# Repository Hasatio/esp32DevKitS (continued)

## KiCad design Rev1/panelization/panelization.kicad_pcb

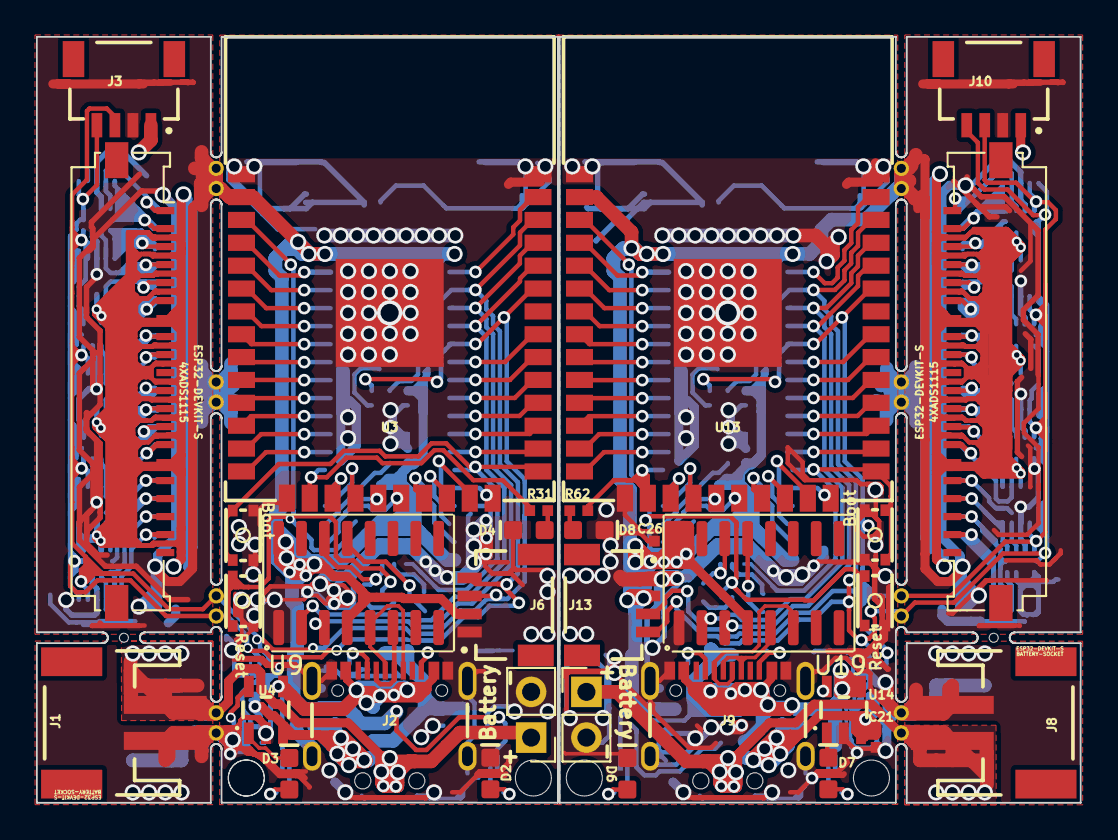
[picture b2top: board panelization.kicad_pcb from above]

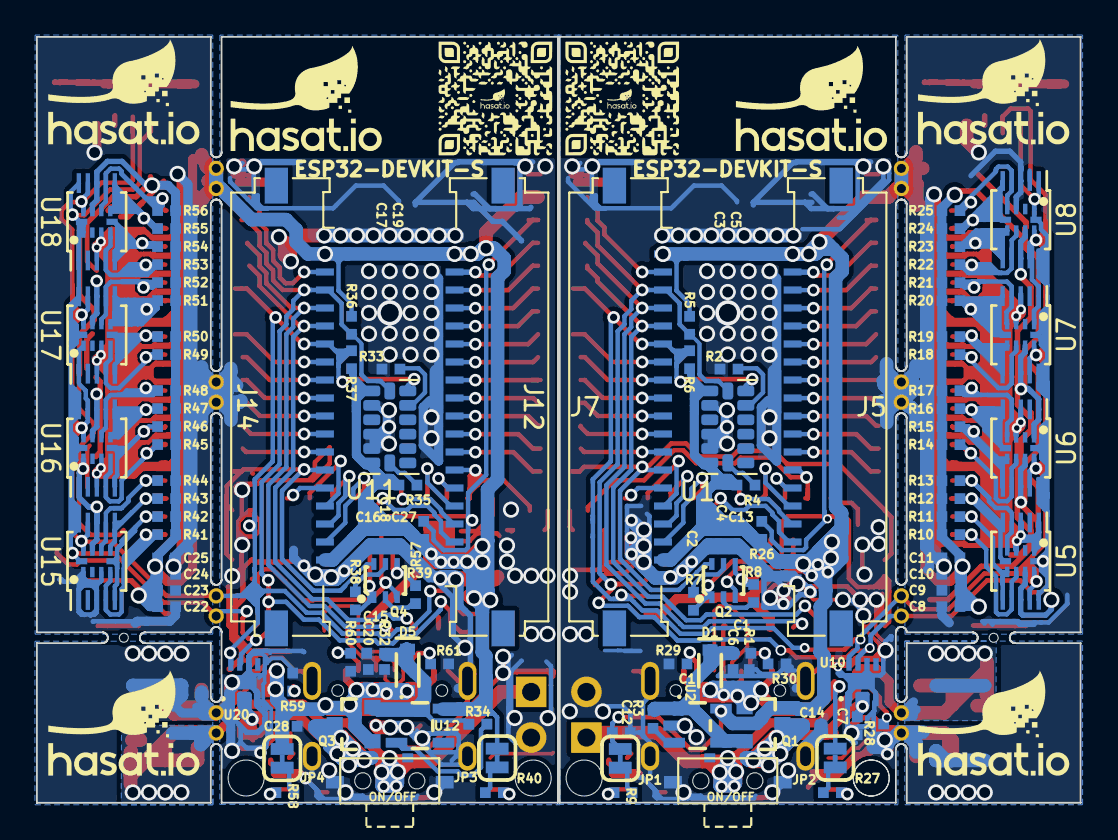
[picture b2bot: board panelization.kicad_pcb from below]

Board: 2 copper layers, 58.0 x 42.5 mm, 164 parts (124 on the bottom side), 146 nets.

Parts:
>NAME: >VALUE; QFN-10-RSE
>NAME#2, >NAME#3, >NAME#4, >NAME#5, >NAME#6, >NAME#7, >NAME#8: >VALUE; QFN-10-RSE
C1, C2, C3, C8, C9, C10, C11, C13, C15, C16, C17, C22, C23, C24, C25, C27: 1.0uF; 0402-TIGHT
C4, C5, C18, C19: 10uF; 0402-TIGHT
C6, C7, C20, C21: 4.7uF; 0402-TIGHT
C12, C14, C26, C28: 0.1uF; 0402-TIGHT
D1, D5: S4 3A/10V/280mV; SOD-323
D2, D6: RED; LED-0603
D3, D7: Yellow; LED-0603
D4, D8: BLUE; LED-0603
J1, J8: JST_2MM_MALE; JST-2-SMD
J2, J9: USB_C_2-LAYER_PADS; USB-C-16P-2LAYER-PADS
J3, J6, J10, J13: QWIIC_RIGHT_ANGLE; JST04_1MM_RA
J4, J5, J7, J11, J12, J14: Conn_01x20; Molex_200528-0200_1x20-1MP_P1.00mm_Horizontal
JP1, JP2, JP3, JP4: JUMPER-SMT_2_NC_TRACE_SILK; SMT-JUMPER_2_NC_TRACE_SILK
Q1, Q3: DMG2305UX 20V/4.2A/52mΩ/1.4W; SOT23-3
Q2, Q4: MBT3904DW1T1; SC70-6
R1, R3, R4, R7, R8, R26, R32, R34, R35, R38, R39, R57: 10k; 0402-TIGHT
R2, R5, R6, R33, R36, R37: 4k7; 0402-TIGHT
R9, R27, R31, R40, R58, R62: 1k; 0402-TIGHT
R10, R11, R12, R13, R14, R15, R16, R17, R18, R19, R20, R21, R22, R23, R24, R25, R41, R42, R43, R44, R45, R46, R47, R48, R49, R50, R51, R52, R53, R54, R55, R56: 150k; 0402-TIGHT
R28, R59: 2.0k; 0402-TIGHT
R29, R30, R60, R61: 5.1k; 0402-TIGHT
S1, S3: Boot; TACTILE_SWITCH_SMD_2.8X1.9MM
S2, S4: Reset; TACTILE_SWITCH_SMD_2.8X1.9MM
SW1, SW2: ON/OFF; SW_SPDT_k3-1295
U1, U11: ADXL345; LGA-14_3x5mm_P0.8mm_LayoutBorder1x6y
U2, U12: SOT23-5
U3, U13: >VALUE; ESP-WROOM-32-NARROW
U4, U14: MCP73831; SOT23-5
U5, U6, U7, U8, U15, U16, U17, U18: ADS1115IDGS; TSSOP-10_3x3mm_P0.5mm
U9, U19: CH340C; SOIC-16_3.9x9.9mm_P1.27mm
U10, U20: MAX17048; DFN-8
mouse-bite-1mm-slot, mouse-bite-1mm-slot#2: VAL**; mouse-bite-1mm x2
mouse-bite-emm-slot: VAL**; mouse-bite-1mm 2
mouse-bite-emm-slot#2, mouse-bite-emm-slot#3, mouse-bite-emm-slot#4, mouse-bite-emm-slot#5, mouse-bite-emm-slot#6, mouse-bite-emm-slot#7, mouse-bite-emm-slot#8: VAL**; mouse-bite-1mm 2

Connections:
Board_0-3.3V: >NAME.8, >NAME#3.8, >NAME#7.1, >NAME#7.8, >NAME#8.8, C2.1, C3.1, C4.1, C5.1, C8.1, C9.1, C10.1, C11.1, C12.1, C13.1, J3.2, J5.2, J5.19, J6.2, J7.2, J7.19, JP1.2, R4.1, R5.1, R6.1, R10.2, R11.2, R12.2, R13.2, R14.2, R15.2, R16.2, R17.2, R18.1, R19.1, R20.1, R21.1, R22.1, R23.1, R24.1, R25.1, R26.1, U1.1 (Vdd_I/O), U1.6 (Vs), U2.5 (OUT), U3.2 (VDD), U5.8 (VDD), U6.1 (ADDR), U6.8 (VDD), U7.8 (VDD), U8.8 (VDD), U9.4 (V3), U9.16 (VCC)
Board_0-/A1: >NAME#8.7, J4.19, R10.1, U5.7 (AIN3)
Board_0-/A2: >NAME#8.6, J4.18, R11.1, U5.6 (AIN2)
Board_0-/A3: >NAME#8.5, J4.17, R12.1, U5.5 (AIN1)
Board_0-/A4: >NAME#8.4, J4.16, R13.1, U5.4 (AIN0)
Board_0-/A5: >NAME#7.7, J4.14, R14.1, U6.7 (AIN3)
Board_0-/A6: >NAME#7.6, J4.13, R15.1, U6.6 (AIN2)
Board_0-/A7: >NAME#7.5, J4.12, R16.1, U6.5 (AIN1)
Board_0-/A8: >NAME#7.4, J4.11, R17.1, U6.4 (AIN0)
Board_0-/A9: >NAME.7, J4.9, R18.2, U7.7 (AIN3)
Board_0-/A10: >NAME.6, J4.8, R19.2, U7.6 (AIN2)
Board_0-/A11: >NAME.5, J4.6, R20.2, U7.5 (AIN1)
Board_0-/A12: >NAME.4, J4.5, R21.2, U7.4 (AIN0)
Board_0-/A13: >NAME#3.7, J4.4, R22.2, U8.7 (AIN3)
Board_0-/A14: >NAME#3.6, J4.3, R23.2, U8.6 (AIN2)
Board_0-/A15: >NAME#3.5, J4.2, R24.2, U8.5 (AIN1)
Board_0-/A16: >NAME#3.4, J4.1, R25.2, U8.4 (AIN0)
Board_0-/CH340-DTR: Q2.1 (E), R7.1, U9.13 (~DTR)
Board_0-/CH340-RTS: Q2.4 (E), R8.1, U9.14 (~RTS)
Board_0-/D+: J2.A6 (D+), J2.B6 (D+), U9.5 (UD+)
Board_0-/D-: J2.A7 (D-), J2.B7 (D-), U9.6 (UD-)
Board_0-/EN: R3.2, U2.3 (EN)
Board_0-/GPIO_0/ADC2_1/QPWR: J7.14, Q2.6 (C), S1.1, S1.3, U3.25 (IO0)
Board_0-/GPIO_1/TX: J7.5, U3.35 (TXD0/IO1), U9.3 (RXD)
Board_0-/GPIO_2/ADC2_2: J7.15, U3.24 (IO2)
Board_0-/GPIO_3/RX: J7.6, U3.34 (RXD0/IO3), U9.2 (TXD)
Board_0-/GPIO_4/ADC2_0: J7.13, U3.26 (IO4)
Board_0-/GPIO_5/SD_CS: J7.10, U3.29 (IO5)
Board_0-/GPIO_6/SCK: J5.3, U3.20 (SCK/CLK)
Board_0-/GPIO_7/SDO: J7.18, U3.21 (SDO/SD0)
Board_0-/GPIO_8/SDI: J7.17, U3.22 (SDI/SD1)
Board_0-/GPIO_9/SHD: J5.6, U3.17 (SHD/SD2)
Board_0-/GPIO_10/SWP: J5.5, U3.18 (SWP/SD3)
Board_0-/GPIO_11/SCS: J5.4, U3.19 (SCS/CMD)
Board_0-/GPIO_12/ADC2_5: J5.8, U3.14 (IO12)
Board_0-/GPIO_13/ADC2_4/LED: J5.7, R31.1, U3.16 (IO13)
Board_0-/GPIO_14/ADC2_6: J5.9, U3.13 (IO14)
Board_0-/GPIO_15/ADC2_3: J7.16, U3.23 (IO15)
Board_0-/GPIO_16/RX: J7.12, U3.27 (IO16)
Board_0-/GPIO_17/TX: J7.11, U3.28 (IO17)
Board_0-/GPIO_18/SCK: J7.9, U3.30 (IO18)
Board_0-/GPIO_19/CIPO: J7.8, U3.31 (IO19)
Board_0-/GPIO_21/SDA: >NAME.1, >NAME.9, >NAME#3.9, >NAME#7.9, >NAME#8.9, J3.3, J6.3, J7.7, R6.2, U1.13 (SDA/SDI/SDIO), U3.33 (IO21), U5.9 (SDA), U6.9 (SDA), U7.1 (ADDR), U7.9 (SDA), U8.9 (SDA), U10.8 (SDA)
Board_0-/GPIO_22/SCL: >NAME.10, >NAME#3.1, >NAME#3.10, >NAME#7.10, >NAME#8.10, J3.4, J6.4, J7.4, R5.2, U1.14 (SCL/SCLK), U3.36 (IO22), U5.10 (SCL), U6.10 (SCL), U7.10 (SCL), U8.1 (ADDR), U8.10 (SCL), U10.7 (SCL)
Board_0-/GPIO_23/COPI: J7.3, U3.37 (IO23)
Board_0-/GPIO_25/ADC2_8: J5.12, U3.10 (IO25)
Board_0-/GPIO_26/ADC2_9: J5.11, U3.11 (IO26)
Board_0-/GPIO_27/ADC2_7: J5.10, U3.12 (IO27)
Board_0-/GPIO_32/ADC1_4: J5.14, U3.8 (IO32)
Board_0-/GPIO_33/ADC1_5: J5.13, U3.9 (IO33)
Board_0-/GPIO_34/ADC1_6: J5.16, U3.6 (IO34)
Board_0-/GPIO_35/ADC1_7: J5.15, U3.7 (IO35)
Board_0-/GPIO_36/ADC1_0: J5.18, U3.4 (SENSOR_VP)
Board_0-/GPIO_39/ADC1_3: J5.17, U3.5 (SENSOR_VN)
Board_0-/V: J1.2 (+), SW1.2 (B)
Board_0-/~RESET: Q2.3 (C), R26.2, S2.1, S2.3, U3.3 (EN)
Board_0-GND: >NAME.3, >NAME#3.3, >NAME#7.3, >NAME#8.1, >NAME#8.3, C1.2, C2.2, C3.2, C4.2, C5.2, C6.2, C7.2, C8.2, C9.2, C10.2, C11.2, C12.2, C13.2, C14.2, D2.C, D4.C, J1.1 (-), J2.GND, J2.GND2 (GND), J2.SHLD1 (SHLD), J2.SHLD2 (SHLD), J2.SHLD3 (SHLD), J2.SHLD4 (SHLD), J3.1, J4.7, J4.15, J5.1, J5.20, J6.1, J7.1, J7.20, R1.1, R2.2, R28.1, R29.1, R30.1, S1.2, S1.4, S2.2, S2.4, SW1.GND, U1.2 (GND), U1.4 (GND), U1.5 (GND), U2.2 (GND), U3.1 (GND), U3.15 (GND), U3.38 (GND), U3.39 (GND), U4.2 (VSS), U5.1 (ADDR), U5.3 (GND), U6.3 (GND), U7.3 (GND), U8.3 (GND), U9.1 (GND), U10.1 (CTG), U10.4 (GND), U10.6 (QSTRT), U10.9 (GND)
Board_0-Net-(D2-PadA): D2.A, R9.2
Board_0-Net-(D3-PadA): D3.A, R27.2
Board_0-Net-(D4-PadA): D4.A, R31.2
Board_0-Net-(J2-CC1): J2.A5 (CC1), R30.2
Board_0-Net-(J2-CC2): J2.B5 (CC2), R29.2
Board_0-Net-(JP1-Pad1): JP1.1, R9.1
Board_0-Net-(JP2-Pad1): JP2.1, R27.1
Board_0-Net-(Q2A-B): Q2.5 (B), R7.2
Board_0-Net-(Q2B-B): Q2.2 (B), R8.2
Board_0-Net-(U1-SDO/ADDR): R2.1, U1.12 (SDO/ADDR)
Board_0-Net-(U1-~CS): R4.2, U1.7 (~CS)
Board_0-Net-(U4-PROG): R28.2, U4.5 (PROG)
Board_0-Net-(U4-STAT): D3.C, U4.1 (STAT)
Board_0-VIN: C1.1, D1.C, Q1.2 (S), R3.1, U2.1 (IN)
Board_0-V_BATT: C7.1, C14.1, Q1.3 (D), SW1.3 (C), U4.3 (VBAT), U10.2 (CELL), U10.3 (VDD)
Board_0-V_USB: C6.1, D1.A, J2.VBUS1 (VBUS), J2.VBUS2 (VBUS), JP2.2, Q1.1 (G), R1.2, U4.4 (VIN)
Board_1-3.3V: >NAME#2.8, >NAME#4.1, >NAME#4.8, >NAME#5.8, >NAME#6.8, C16.1, C17.1, C18.1, C19.1, C22.1, C23.1, C24.1, C25.1, C26.1, C27.1, J10.2, J12.2, J12.19, J13.2, J14.2, J14.19, JP3.2, R35.1, R36.1, R37.1, R41.2, R42.2, R43.2, R44.2, R45.2, R46.2, R47.2, R48.2, R49.1, R50.1, R51.1, R52.1, R53.1, R54.1, R55.1, R56.1, R57.1, U11.1 (Vdd_I/O), U11.6 (Vs), U12.5 (OUT), U13.2 (VDD), U15.8 (VDD), U16.1 (ADDR), U16.8 (VDD), U17.8 (VDD), U18.8 (VDD), U19.4 (V3), U19.16 (VCC)
Board_1-/A1: >NAME#6.4, J11.2, R41.1, U15.4 (AIN0)
Board_1-/A2: >NAME#6.5, J11.3, R42.1, U15.5 (AIN1)
Board_1-/A3: >NAME#6.6, J11.4, R43.1, U15.6 (AIN2)
Board_1-/A4: >NAME#6.7, J11.5, R44.1, U15.7 (AIN3)
Board_1-/A5: >NAME#4.4, J11.7, R45.1, U16.4 (AIN0)
Board_1-/A6: >NAME#4.5, J11.8, R46.1, U16.5 (AIN1)
Board_1-/A7: >NAME#4.6, J11.9, R47.1, U16.6 (AIN2)
Board_1-/A8: >NAME#4.7, J11.10, R48.1, U16.7 (AIN3)
Board_1-/A9: >NAME#5.4, J11.12, R49.2, U17.4 (AIN0)
Board_1-/A10: >NAME#5.5, J11.13, R50.2, U17.5 (AIN1)
Board_1-/A11: >NAME#5.6, J11.15, R51.2, U17.6 (AIN2)
Board_1-/A12: >NAME#5.7, J11.16, R52.2, U17.7 (AIN3)
Board_1-/A13: >NAME#2.4, J11.17, R53.2, U18.4 (AIN0)
Board_1-/A14: >NAME#2.5, J11.18, R54.2, U18.5 (AIN1)
Board_1-/A15: >NAME#2.6, J11.19, R55.2, U18.6 (AIN2)
Board_1-/A16: >NAME#2.7, J11.20, R56.2, U18.7 (AIN3)
Board_1-/CH340-DTR: Q4.1 (E), R38.1, U19.13 (~DTR)
Board_1-/CH340-RTS: Q4.4 (E), R39.1, U19.14 (~RTS)
Board_1-/D+: J9.A6 (D+), J9.B6 (D+), U19.5 (UD+)
Board_1-/D-: J9.A7 (D-), J9.B7 (D-), U19.6 (UD-)
Board_1-/EN: R34.2, U12.3 (EN)
Board_1-/GPIO_0/ADC2_1/QPWR: J14.14, Q4.6 (C), S3.1, S3.3, U13.25 (IO0)
Board_1-/GPIO_1/TX: J14.5, U13.35 (TXD0/IO1), U19.3 (RXD)
Board_1-/GPIO_2/ADC2_2: J14.15, U13.24 (IO2)
Board_1-/GPIO_3/RX: J14.6, U13.34 (RXD0/IO3), U19.2 (TXD)
Board_1-/GPIO_4/ADC2_0: J14.13, U13.26 (IO4)
Board_1-/GPIO_5/SD_CS: J14.10, U13.29 (IO5)
Board_1-/GPIO_6/SCK: J12.3, U13.20 (SCK/CLK)
Board_1-/GPIO_7/SDO: J14.18, U13.21 (SDO/SD0)
Board_1-/GPIO_8/SDI: J14.17, U13.22 (SDI/SD1)
Board_1-/GPIO_9/SHD: J12.6, U13.17 (SHD/SD2)
Board_1-/GPIO_10/SWP: J12.5, U13.18 (SWP/SD3)
Board_1-/GPIO_11/SCS: J12.4, U13.19 (SCS/CMD)
Board_1-/GPIO_12/ADC2_5: J12.8, U13.14 (IO12)
Board_1-/GPIO_13/ADC2_4/LED: J12.7, R62.1, U13.16 (IO13)
Board_1-/GPIO_14/ADC2_6: J12.9, U13.13 (IO14)
Board_1-/GPIO_15/ADC2_3: J14.16, U13.23 (IO15)
Board_1-/GPIO_16/RX: J14.12, U13.27 (IO16)
Board_1-/GPIO_17/TX: J14.11, U13.28 (IO17)
Board_1-/GPIO_18/SCK: J14.9, U13.30 (IO18)
Board_1-/GPIO_19/CIPO: J14.8, U13.31 (IO19)
Board_1-/GPIO_21/SDA: >NAME#2.9, >NAME#4.9, >NAME#5.1, >NAME#5.9, >NAME#6.9, J10.3, J13.3, J14.7, R37.2, U11.13 (SDA/SDI/SDIO), U13.33 (IO21), U15.9 (SDA), U16.9 (SDA), U17.1 (ADDR), U17.9 (SDA), U18.9 (SDA), U20.8 (SDA)
Board_1-/GPIO_22/SCL: >NAME#2.1, >NAME#2.10, >NAME#4.10, >NAME#5.10, >NAME#6.10, J10.4, J13.4, J14.4, R36.2, U11.14 (SCL/SCLK), U13.36 (IO22), U15.10 (SCL), U16.10 (SCL), U17.10 (SCL), U18.1 (ADDR), U18.10 (SCL), U20.7 (SCL)
Board_1-/GPIO_23/COPI: J14.3, U13.37 (IO23)
Board_1-/GPIO_25/ADC2_8: J12.12, U13.10 (IO25)
Board_1-/GPIO_26/ADC2_9: J12.11, U13.11 (IO26)
Board_1-/GPIO_27/ADC2_7: J12.10, U13.12 (IO27)
Board_1-/GPIO_32/ADC1_4: J12.14, U13.8 (IO32)
Board_1-/GPIO_33/ADC1_5: J12.13, U13.9 (IO33)
Board_1-/GPIO_34/ADC1_6: J12.16, U13.6 (IO34)
Board_1-/GPIO_35/ADC1_7: J12.15, U13.7 (IO35)
Board_1-/GPIO_36/ADC1_0: J12.18, U13.4 (SENSOR_VP)
Board_1-/GPIO_39/ADC1_3: J12.17, U13.5 (SENSOR_VN)
Board_1-/V: J8.2 (+), SW2.2 (B)
Board_1-/~RESET: Q4.3 (C), R57.2, S4.1, S4.3, U13.3 (EN)
Board_1-GND: >NAME#2.3, >NAME#4.3, >NAME#5.3, >NAME#6.1, >NAME#6.3, C15.2, C16.2, C17.2, C18.2, C19.2, C20.2, C21.2, C22.2, C23.2, C24.2, C25.2, C26.2, C27.2, C28.2, D6.C, D8.C, J8.1 (-), J9.GND, J9.GND2 (GND), J9.SHLD1 (SHLD), J9.SHLD2 (SHLD), J9.SHLD3 (SHLD), J9.SHLD4 (SHLD), J10.1, J11.6, J11.14, J12.1, J12.20, J13.1, J14.1, J14.20, R32.1, R33.2, R59.1, R60.1, R61.1, S3.2, S3.4, S4.2, S4.4, SW2.GND, U11.2 (GND), U11.4 (GND), U11.5 (GND), U12.2 (GND), U13.1 (GND), U13.15 (GND), U13.38 (GND), U13.39 (GND), U14.2 (VSS), U15.1 (ADDR), U15.3 (GND), U16.3 (GND), U17.3 (GND), U18.3 (GND), U19.1 (GND), U20.1 (CTG), U20.4 (GND), U20.6 (QSTRT), U20.9 (GND)
Board_1-Net-(D6-PadA): D6.A, R40.2
Board_1-Net-(D7-PadA): D7.A, R58.2
Board_1-Net-(D8-PadA): D8.A, R62.2
Board_1-Net-(J9-CC1): J9.A5 (CC1), R61.2
Board_1-Net-(J9-CC2): J9.B5 (CC2), R60.2
Board_1-Net-(JP3-Pad1): JP3.1, R40.1
Board_1-Net-(JP4-Pad1): JP4.1, R58.1
Board_1-Net-(Q4A-B): Q4.5 (B), R38.2
Board_1-Net-(Q4B-B): Q4.2 (B), R39.2
Board_1-Net-(U11-SDO/ADDR): R33.1, U11.12 (SDO/ADDR)
Board_1-Net-(U11-~CS): R35.2, U11.7 (~CS)
Board_1-Net-(U14-PROG): R59.2, U14.5 (PROG)
Board_1-Net-(U14-STAT): D7.C, U14.1 (STAT)
Board_1-VIN: C15.1, D5.C, Q3.2 (S), R34.1, U12.1 (IN)
Board_1-V_BATT: C21.1, C28.1, Q3.3 (D), SW2.1 (A), U14.3 (VBAT), U20.2 (CELL), U20.3 (VDD)
Board_1-V_USB: C20.1, D5.A, J9.VBUS1 (VBUS), J9.VBUS2 (VBUS), JP4.2, Q3.1 (G), R32.2, U14.4 (VIN)

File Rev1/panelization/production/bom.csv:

Designator,Footprint,Quantity,Value,LCSC Part #
"_5, _4, _3, _2, ",,5,,
"C1, C10, C11, C13, C15, C16, C17, C2, C22, C23, C24, C25, C27, C3, C8, C9",0402-TIGHT,16,1.0uF,
"C12, C14, C26, C28",0402-TIGHT,4,0.1uF,
"C18, C19, C4, C5",0402-TIGHT,4,10uF,
"C20, C21, C6, C7",0402-TIGHT,4,4.7uF,
"D1, D5",SOD-323,2,S4 3A/10V/280mV,
"D2, D6",LED-0603,2,RED,
"D3, D7",LED-0603,2,Yellow,
"D4, D8",LED-0603,2,BLUE,
"J1, J8",JST-2-SMD,2,JST_2MM_MALE,
"J10, J13, J3, J6",JST04_1MM_RA,4,QWIIC_RIGHT_ANGLE,
"J11, J12, J14, J4, J5, J7",Molex_200528-0200_1x20-1MP_P1.00mm_Horizontal,6,Conn_01x20,
"J2, J9",USB-C-16P-2LAYER-PADS,2,USB_C_2-LAYER_PADS,
"JP1, JP2, JP3, JP4",SMT-JUMPER_2_NC_TRACE_SILK,4,JUMPER-SMT_2_NC_TRACE_SILK,
"Q1, Q3",SOT23-3,2,DMG2305UX 20V/4.2A/52mΩ/1.4W,
"Q2, Q4",SC70-6,2,MBT3904DW1T1,
"R1, R26, R3, R32, R34, R35, R38, R39, R4, R57, R7, R8",0402-TIGHT,12,10k,
"R10, R11, R12, R13, R14, R15, R16, R17, R18, R19, R20, R21, R22, R23, R24, R25, R41, R42, R43, R44, R45, R46, R47, R48, R49, R50, R51, R52, R53, R54, R55, R56",0402-TIGHT,32,150k,
"R2, R33, R36, R37, R5, R6",0402-TIGHT,6,4k7,
"R27, R31, R40, R58, R62, R9",0402-TIGHT,6,1k,
"R28, R59",0402-TIGHT,2,2.0k,
"R29, R30, R60, R61",0402-TIGHT,4,5.1k,
"S1, S3",TACTILE_SWITCH_SMD_2.8X1.9MM,2,Boot,
"S2, S4",TACTILE_SWITCH_SMD_2.8X1.9MM,2,Reset,
"SW1, SW2",SW_SPDT_k3-1295,2,ON/OFF,
"U1, U11",LGA-14_3x5mm_P0.8mm_LayoutBorder1x6y,2,ADXL345,
"U10, U20",DFN-8,2,MAX17048,
"U12, U2",SOT23-5,2,AP2112K-3.3,
"U13, U3",ESP-WROOM-32-NARROW,2,>VALUE,
"U14, U4",SOT23-5,2,MCP73831,
"U15, U16, U17, U18, U5, U6, U7, U8",TSSOP-10_3x3mm_P0.5mm,8,ADS1115IDGS,
"U19, U9",SOIC-16_3.9x9.9mm_P1.27mm,2,CH340C,

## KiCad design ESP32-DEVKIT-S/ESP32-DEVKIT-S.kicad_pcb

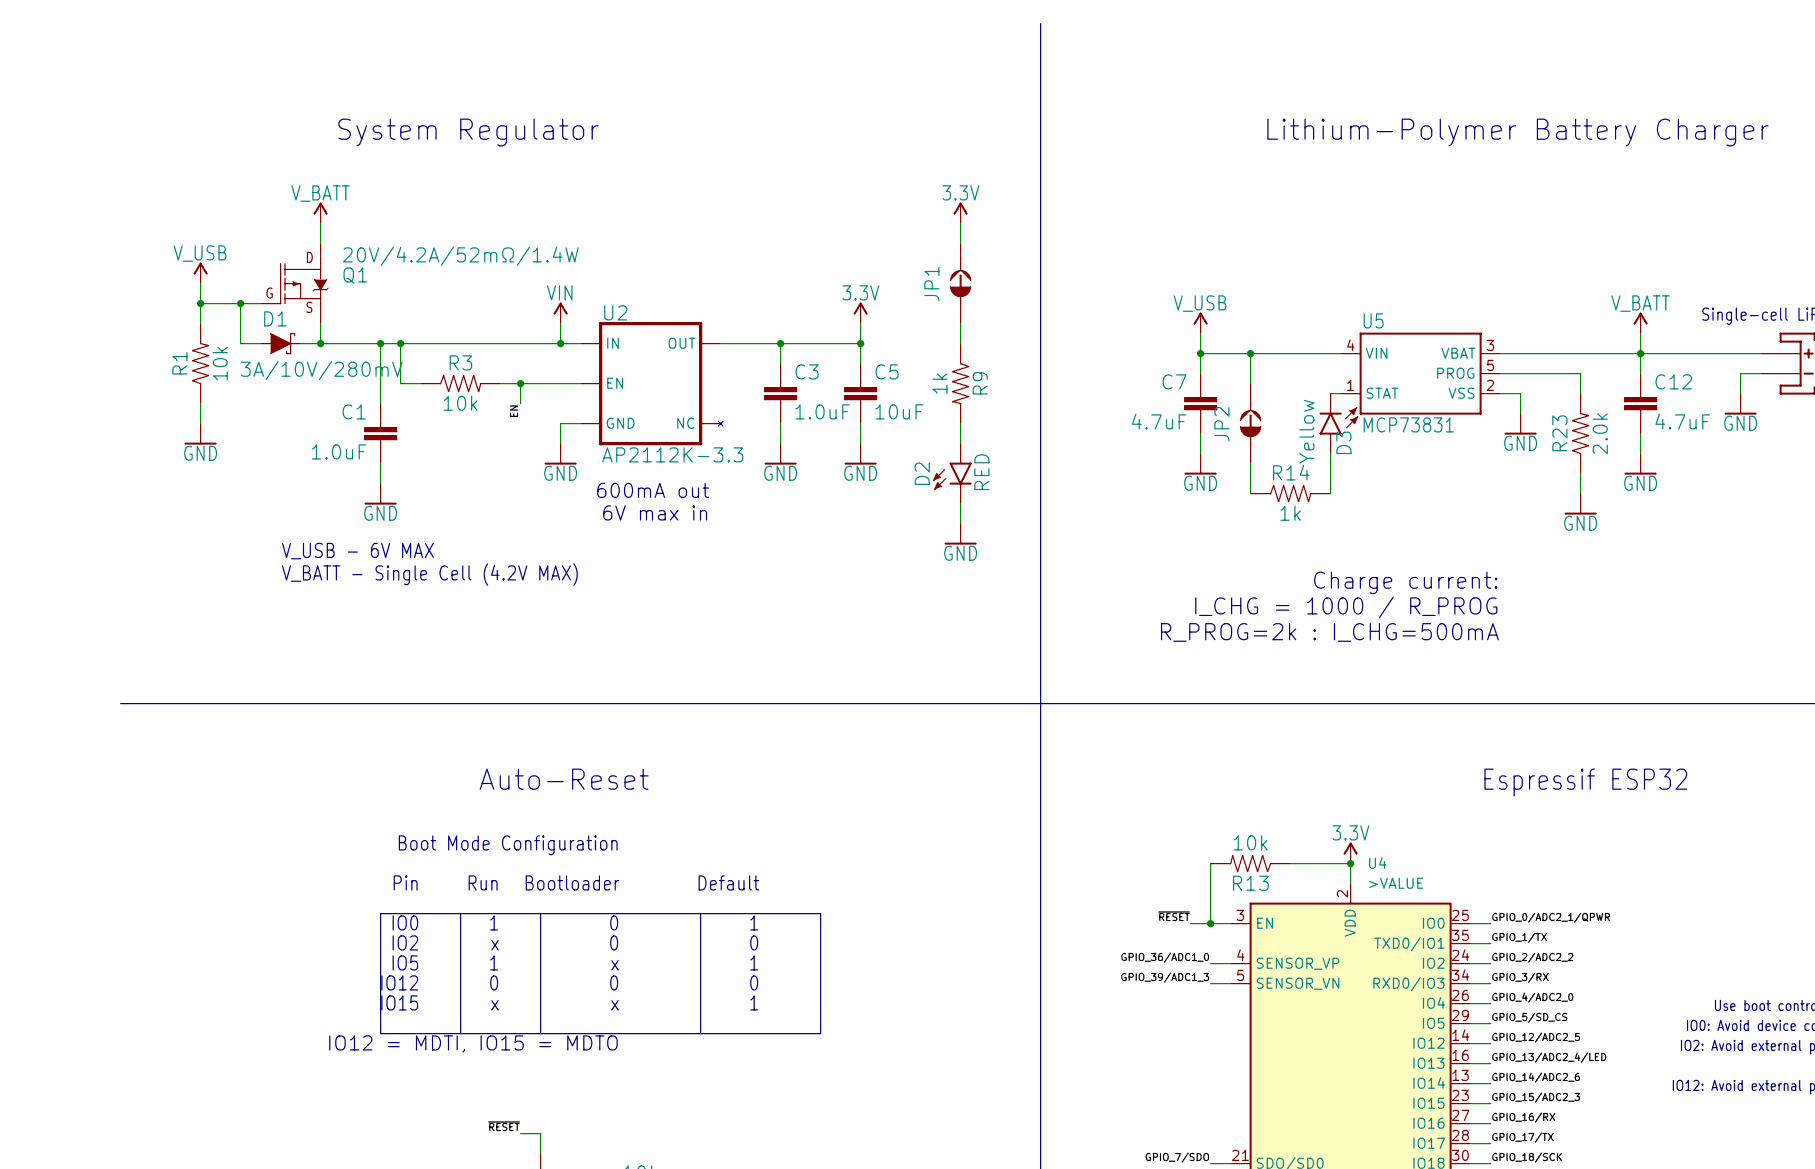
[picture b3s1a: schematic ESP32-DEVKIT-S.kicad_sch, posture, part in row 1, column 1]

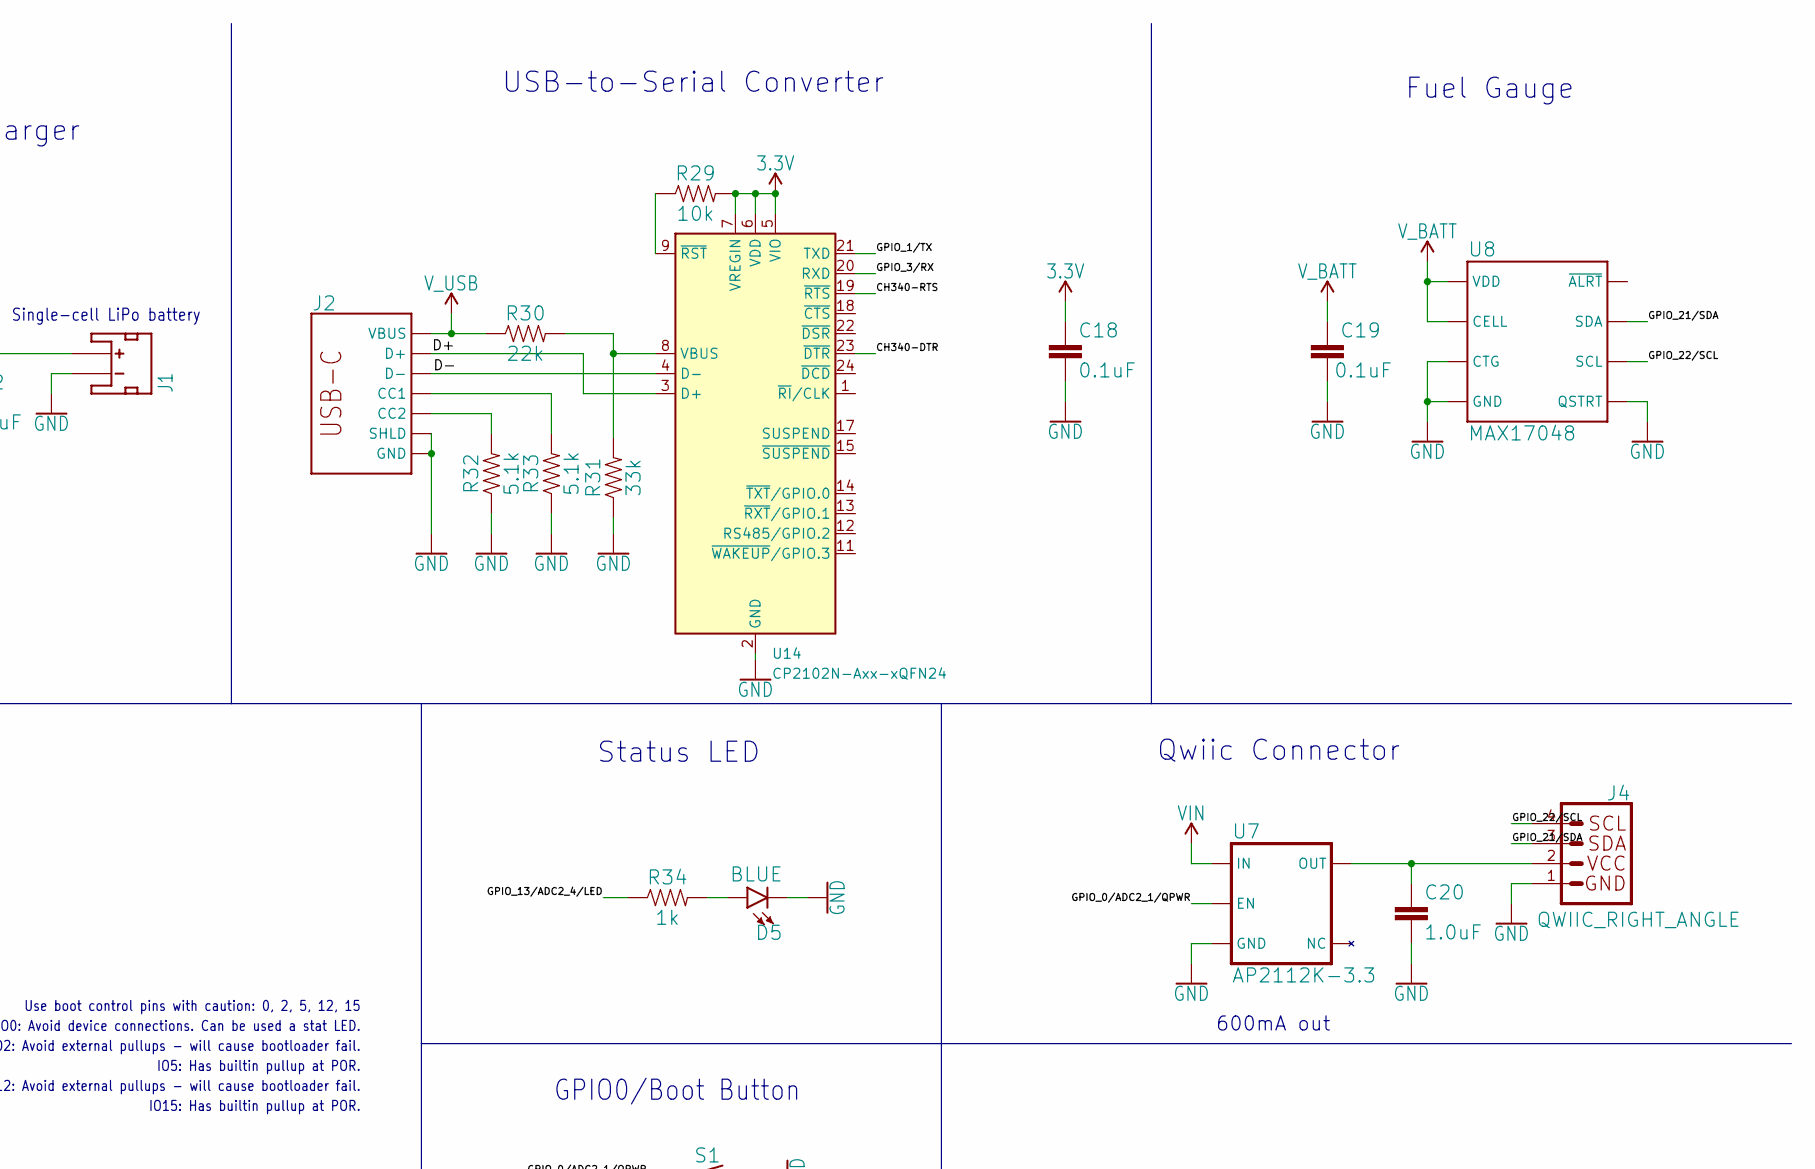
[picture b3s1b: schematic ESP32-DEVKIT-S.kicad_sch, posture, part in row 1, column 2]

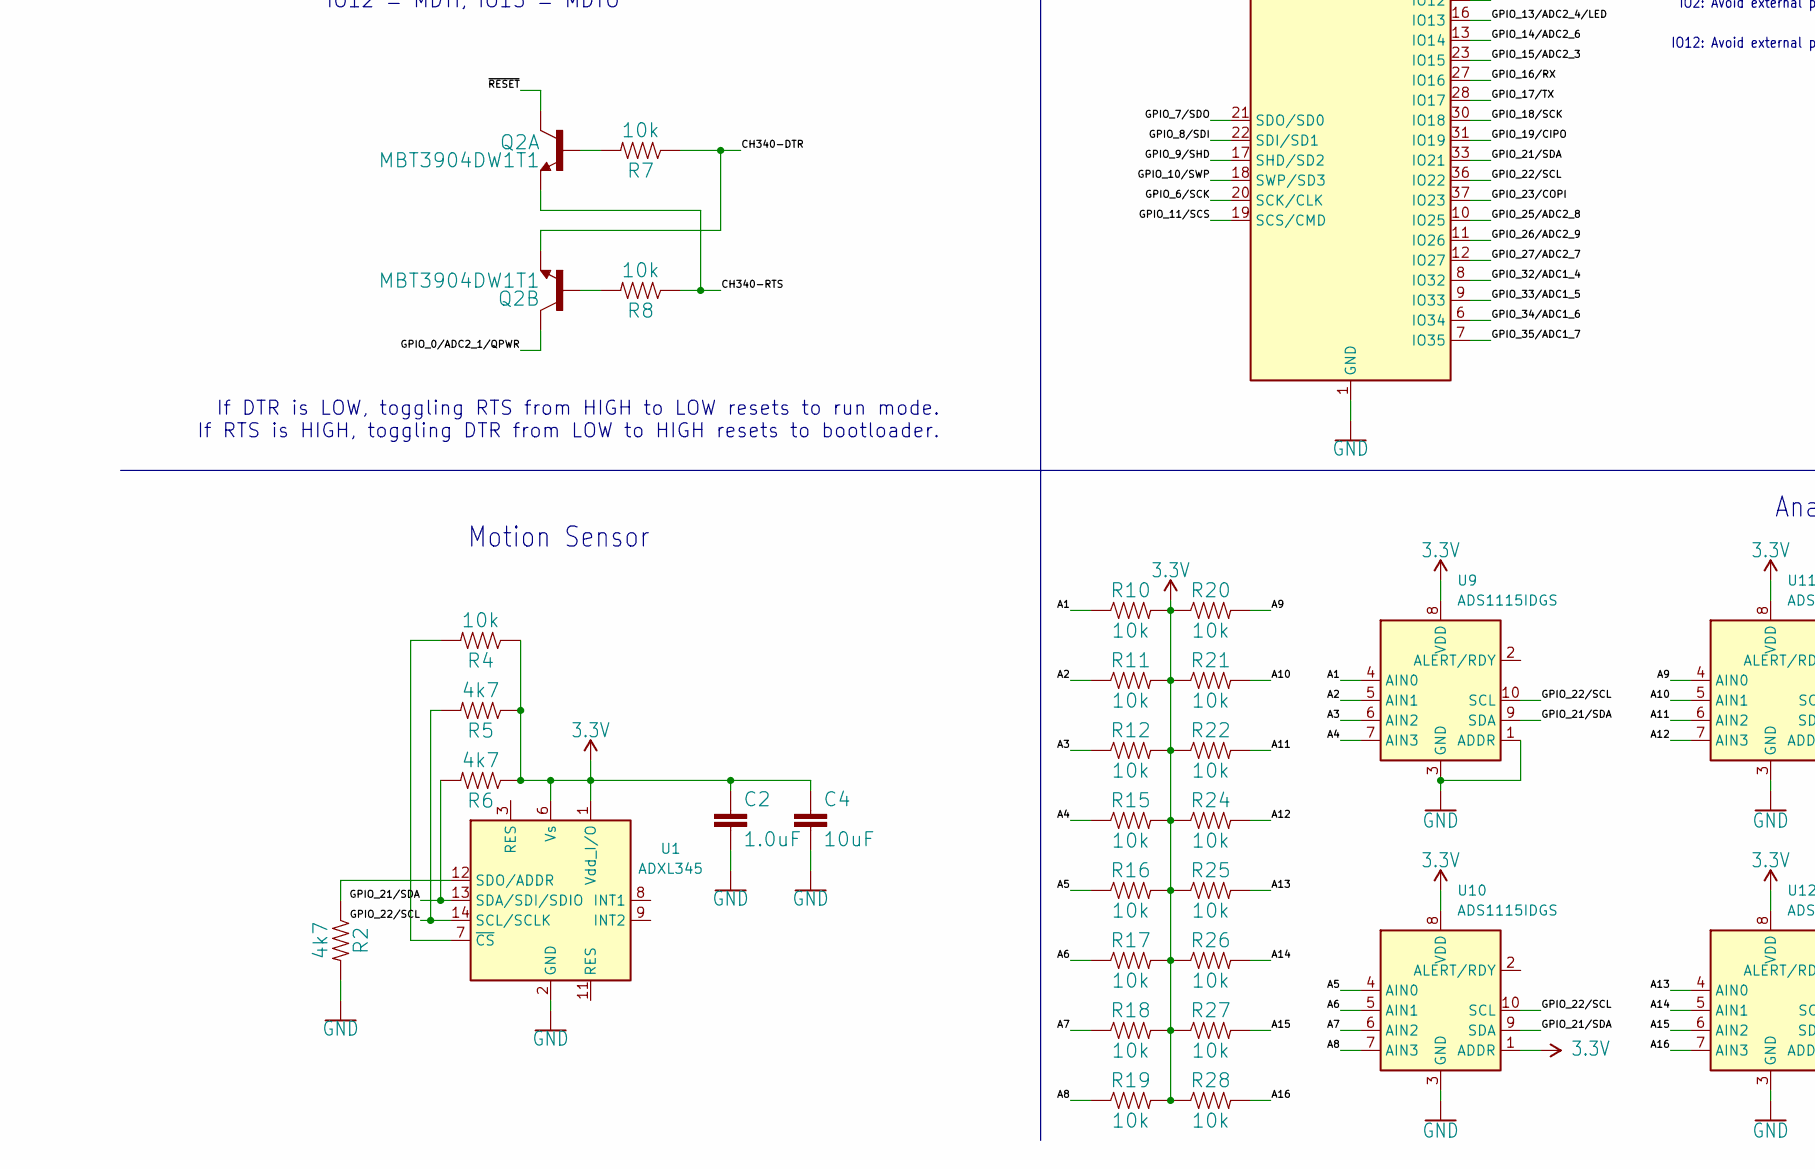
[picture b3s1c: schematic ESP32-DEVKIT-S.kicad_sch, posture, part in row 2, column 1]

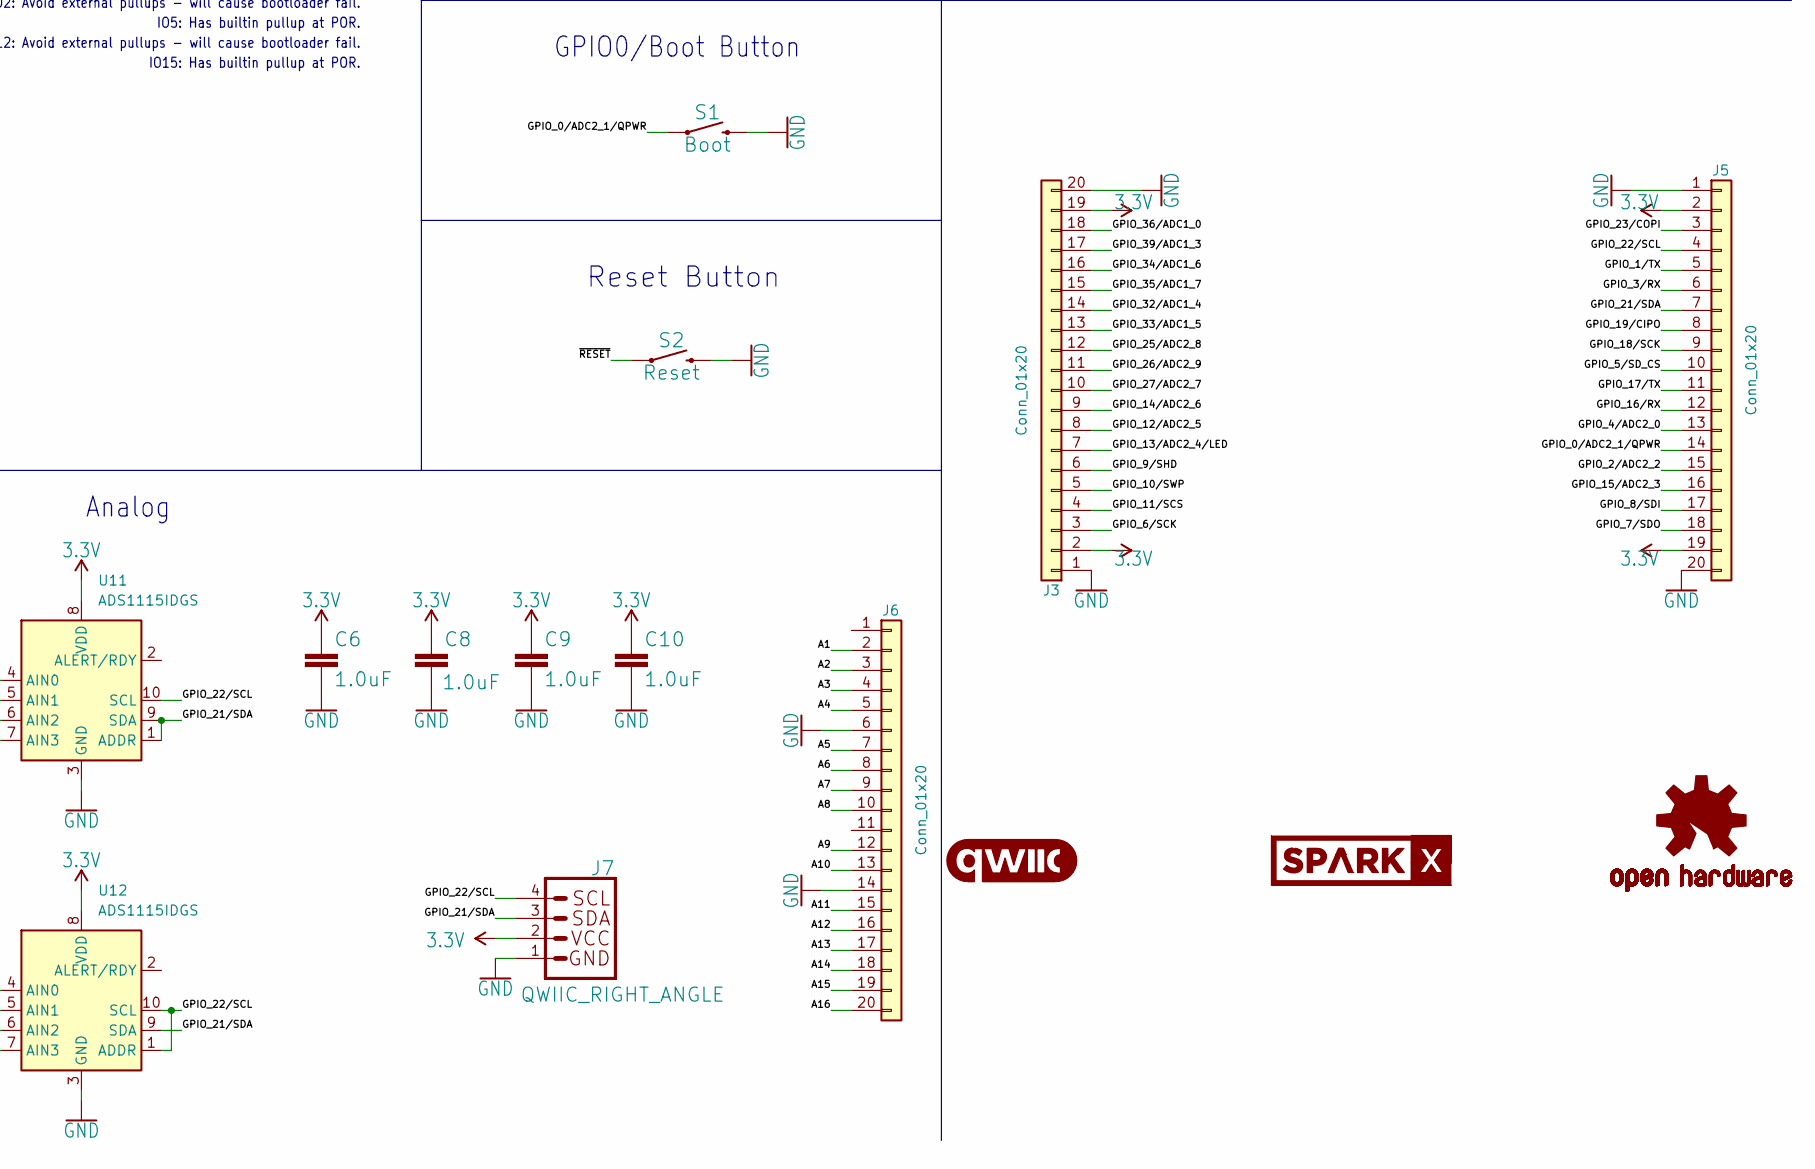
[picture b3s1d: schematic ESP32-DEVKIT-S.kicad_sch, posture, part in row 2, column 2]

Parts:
C1, C2, C3, C6, C8, C9, C10, C20: 1.0uF; 0402-TIGHT
C4, C5: 10uF; 0402-TIGHT
C7: 4.7uF; 0603
C12: 4.7uF; 0402-TIGHT
C18, C19: 0.1uF; 0402-TIGHT
D1: 3A/10V/280mV; SOD-323
D2: RED; LED-0603
D3: Yellow; LED-0603
D5: BLUE; LED-0603
J1: JST_2MM_MALE; JST-2-SMD
J2: USB_C_2-LAYER_PADS; USB-C-16P-2LAYER-PADS
J3, J5, J6: Conn_01x20; Molex_200528-0200_1x20-1MP_P1.00mm_Horizontal
J4, J7: QWIIC_RIGHT_ANGLE; JST04_1MM_RA
JP1, JP2: JUMPER-SMT_2_NC_TRACE_SILK; SMT-JUMPER_2_NC_TRACE_SILK
LOGO1: QWIIC_LOGO_4MM; QWIIC_4MM
LOGO2: OSHW-LOGOMINI; OSHW-LOGO-MINI
Q1: 20V/4.2A/52mΩ/1.4W; SOT23-3
Q2: MBT3904DW1T1; SC70-6
R1, R3, R4, R7, R8, R10, R11, R12, R13, R15, R16, R17, R18, R19, R20, R21, R22, R24, R25, R26, R27, R28, R29: 10k; 0402-TIGHT
R2, R5, R6: 4k7; 0402-TIGHT
R9, R14, R34: 1k; 0402-TIGHT
R23: 2.0k; 0603
R30: 22k; 0402-TIGHT
R31: 33k; 0402-TIGHT
R32, R33: 5.1k; 0402-TIGHT
S1: Boot; TACTILE_SWITCH_SMD_4.6X2.8MM
S2: Reset; TACTILE_SWITCH_SMD_4.6X2.8MM
U1: ADXL345; LGA-14_3x5mm_P0.8mm_LayoutBorder1x6y
U2, U7: SOT23-5
U4: >VALUE; ESP-WROOM-32-NARROW
U5: MCP73831; SOT23-5
U8: MAX17048; DFN-8
U9, U10, U11, U12: ADS1115IDGS; TSSOP-10_3x3mm_P0.5mm
U14: CP2102N-Axx-xQFN24; QFN-24-1EP_4x4mm_P0.5mm_EP2.6x2.6mm
U$1: SPARKX-LOGO4; SPARKX-MEDIUM

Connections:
3.3V: C2.1, C3.1, C4.1, C5.1, C6.1, C8.1, C9.1, C10.1, C18.1, J3.2, J3.19, J5.2, J5.19, J7.2, JP1.2, R4.1, R5.1, R6.1, R10.2, R11.2, R12.2, R13.1, R15.2, R16.2, R17.2, R18.2, R19.2, R20.1, R21.1, R22.1, R24.1, R25.1, R26.1, R27.1, R28.1, R29.2, U1.1 (Vdd_I/O), U1.6 (Vs), U2.5 (OUT), U4.2 (VDD), U9.8 (VDD), U10.1 (ADDR), U10.8 (VDD), U11.8 (VDD), U12.8 (VDD), U14.5 (VIO), U14.6 (VDD), U14.7 (VREGIN)
/A1: J6.2, R10.1, U9.4 (AIN0)
/A2: J6.3, R11.1, U9.5 (AIN1)
/A3: J6.4, R12.1, U9.6 (AIN2)
/A4: J6.5, R15.1, U9.7 (AIN3)
/A5: J6.7, R16.1, U10.4 (AIN0)
/A6: J6.8, R17.1, U10.5 (AIN1)
/A7: J6.9, R18.1, U10.6 (AIN2)
/A8: J6.10, R19.1, U10.7 (AIN3)
/A9: J6.12, R20.2, U11.4 (AIN0)
/A10: J6.13, R21.2, U11.5 (AIN1)
/A11: J6.15, R22.2, U11.6 (AIN2)
/A12: J6.16, R24.2, U11.7 (AIN3)
/A13: J6.17, R25.2, U12.4 (AIN0)
/A14: J6.18, R26.2, U12.5 (AIN1)
/A15: J6.19, R27.2, U12.6 (AIN2)
/A16: J6.20, R28.2, U12.7 (AIN3)
/CH340-DTR: Q2.1 (E), R7.1, U14.23 (~DTR)
/CH340-RTS: Q2.4 (E), R8.1, U14.19 (~RTS)
/D+: J2.A6 (D+), J2.B6 (D+), U14.3 (D+)
/D-: J2.A7 (D-), J2.B7 (D-), U14.4 (D-)
/EN: R3.2, U2.3 (EN)
/GPIO_0/ADC2_1/QPWR: J5.14, Q2.6 (C), S1.1, S1.2 (1), U4.25 (IO0), U7.3 (EN)
/GPIO_1/TX: J5.5, U4.35 (TXD0/IO1), U14.21 (TXD)
/GPIO_2/ADC2_2: J5.15, U4.24 (IO2)
/GPIO_3/RX: J5.6, U4.34 (RXD0/IO3), U14.20 (RXD)
/GPIO_4/ADC2_0: J5.13, U4.26 (IO4)
/GPIO_5/SD_CS: J5.10, U4.29 (IO5)
/GPIO_6/SCK: J3.3, U4.20 (SCK/CLK)
/GPIO_7/SDO: J5.18, U4.21 (SDO/SD0)
/GPIO_8/SDI: J5.17, U4.22 (SDI/SD1)
/GPIO_9/SHD: J3.6, U4.17 (SHD/SD2)
/GPIO_10/SWP: J3.5, U4.18 (SWP/SD3)
/GPIO_11/SCS: J3.4, U4.19 (SCS/CMD)
/GPIO_12/ADC2_5: J3.8, U4.14 (IO12)
/GPIO_13/ADC2_4/LED: J3.7, R34.1, U4.16 (IO13)
/GPIO_14/ADC2_6: J3.9, U4.13 (IO14)
/GPIO_15/ADC2_3: J5.16, U4.23 (IO15)
/GPIO_16/RX: J5.12, U4.27 (IO16)
/GPIO_17/TX: J5.11, U4.28 (IO17)
/GPIO_18/SCK: J5.9, U4.30 (IO18)
/GPIO_19/CIPO: J5.8, U4.31 (IO19)
/GPIO_21/SDA: J4.3, J5.7, J7.3, R6.2, U1.13 (SDA/SDI/SDIO), U4.33 (IO21), U8.8 (SDA), U9.9 (SDA), U10.9 (SDA), U11.1 (ADDR), U11.9 (SDA), U12.9 (SDA)
/GPIO_22/SCL: J4.4, J5.4, J7.4, R5.2, U1.14 (SCL/SCLK), U4.36 (IO22), U8.7 (SCL), U9.10 (SCL), U10.10 (SCL), U11.10 (SCL), U12.1 (ADDR), U12.10 (SCL)
/GPIO_23/COPI: J5.3, U4.37 (IO23)
/GPIO_25/ADC2_8: J3.12, U4.10 (IO25)
/GPIO_26/ADC2_9: J3.11, U4.11 (IO26)
/GPIO_27/ADC2_7: J3.10, U4.12 (IO27)
/GPIO_32/ADC1_4: J3.14, U4.8 (IO32)
/GPIO_33/ADC1_5: J3.13, U4.9 (IO33)
/GPIO_34/ADC1_6: J3.16, U4.6 (IO34)
/GPIO_35/ADC1_7: J3.15, U4.7 (IO35)
/GPIO_36/ADC1_0: J3.18, U4.4 (SENSOR_VP)
/GPIO_39/ADC1_3: J3.17, U4.5 (SENSOR_VN)
/~RESET: Q2.3 (C), R13.2, S2.1, S2.2 (1), U4.3 (EN)
GND: C1.2, C2.2, C3.2, C4.2, C5.2, C6.2, C7.2, C8.2, C9.2, C10.2, C12.2, C18.2, C19.2, C20.2, D2.C, D5.C, J1.1 (-), J2.GND, J2.GND2 (GND), J2.SHLD1 (SHLD), J2.SHLD2 (SHLD), J2.SHLD3 (SHLD), J2.SHLD4 (SHLD), J3.1, J3.20, J4.1, J5.1, J5.20, J6.6, J6.14, J7.1, R1.1, R2.2, R23.1, R31.1, R32.1, R33.1, S1.3 (2), S1.4 (2), S2.3 (2), S2.4 (2), U1.2 (GND), U1.4 (GND), U1.5 (GND), U2.2 (GND), U4.1 (GND), U4.15 (GND), U4.38 (GND), U4.39 (GND), U4.GND, U5.2 (VSS), U7.2 (GND), U8.1 (CTG), U8.4 (GND), U8.6 (QSTRT), U8.9 (GND), U9.1 (ADDR), U9.3 (GND), U10.3 (GND), U11.3 (GND), U12.3 (GND), U14.2 (GND), U14.25 (GND)
unnamed: D2.A, R9.2
unnamed: D3.A, R14.2
unnamed: D5.A, R34.2
unnamed: J2.A5 (CC1), R33.2
unnamed: J2.B5 (CC2), R32.2
unnamed: JP1.1, R9.1
unnamed: JP2.1, R14.1
unnamed: Q2.5 (B), R7.2
unnamed: Q2.2 (B), R8.2
unnamed: R2.1, U1.12 (SDO/ADDR)
unnamed: R4.2, U1.7 (~CS)
unnamed: R23.2, U5.5 (PROG)
unnamed: D3.C, U5.1 (STAT)
unnamed: C20.1, J4.2, U7.5 (OUT)
unnamed: R30.2, R31.2, U14.8 (VBUS)
unnamed: R29.1, U14.9 (~RST)
VIN: C1.1, D1.C, Q1.2 (S), R3.1, U2.1 (IN), U7.1 (IN)
V_BATT: C12.1, C19.1, J1.2 (+), Q1.3 (D), U5.3 (VBAT), U8.2 (CELL), U8.3 (VDD)
V_USB: C7.1, D1.A, J2.VBUS1 (VBUS), J2.VBUS2 (VBUS), JP2.2, Q1.1 (G), R1.2, R30.1, U5.4 (VIN)

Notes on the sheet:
Fuel Gauge
Auto-Reset
IO15
Boot Mode Configuration
Reset Button
Default
Pin
IO5: Has builtin pullup at POR.
IO5
Run
Qwiic Connector
IO0
V_USB - 6V MAX V_BATT - Single Cell (4.2V MAX)
Lithium-Polymer Battery Charger
IO2
IO12: Avoid external pullups - will cause bootloader fail.
Espressif ESP32
IO12
USB-to-Serial Converter
IO15: Has builtin pullup at POR.
Motion Sensor
Analog
Status LED
Bootloader
Use boot control pins with caution: 0, 2, 5, 12, 15
GPIO0/Boot Button
Charge current: I_CHG = 1000 / R_PROG R_PROG=2k : I_CHG=500mA
Single-cell LiPo battery
IO0: Avoid device connections. Can be used a stat LED.
600mA out
600mA out 6V max in
If DTR is LOW, toggling RTS from HIGH to LOW resets to run mode. If RTS is HIGH, toggling DTR from LOW to HIGH resets to bootloader.
IO2: Avoid external pullups - will cause bootloader fail.
IO12 = MDTI, IO15 = MDTO
System Regulator
